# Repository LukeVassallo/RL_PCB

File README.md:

[toc]

# Project Description

RL_PCB is an end-to-end Reinforcement Learning PCB placement methodology. The solution is inspired from cellular automata. The state of the circuit placement problem is distributed across all the components on the layout region. Every component can update it's positioning independently based on local and global information. The question of how to update the state, factoring in experience (i.e. past knowledge) is a particularly difficult one. We use reinforcement learning to learn ways of updating the state. We do so in a way that localised updates are not destructive to the global solution. Consequently the solution naturally comes out as an emergent property of the system.  

You can learn more about this work by reading our [DATE 24 paper](https://ieeexplore.ieee.org/document/10546526). My [Master thesis](https://www.lukevassallo.com/wp-content/uploads/2023/09/automated_pcb_component_placement_using_rl_msc_thesis_v2_1_lv.pdf) investigated "A graph placement methodology for fast chip design" proposed by Mirhoseini et al., and based on it's shortcomings proposed this solution. 

If you find this work useful please cite us!
```bibtex
@inproceedings{Vassallo2024,
  author={Vassallo, Luke and Bajada, Josef},
  booktitle={2024 Design, Automation & Test in Europe Conference & Exhibition (DATE)}, 
  title={Learning Circuit Placement Techniques Through Reinforcement Learning with Adaptive Rewards}, 
  year={2024},
  volume={},
  number={},
  pages={1-6},
}
```

RL\_PCB is a novel learning-based method for optimising the placement of circuit components on a Printed Circuit Board (PCB). Reinforcement learning is used to learn general policies for iteratively improving a circuit placement, leading to intuitive layouts while outperforming stochastic methods in terms of post-routing wirelength.

# Key Results

The main contribution of this work is:
1. The policies learn the fundamental rules of the task and demonstrate an understanding of the problem dynamics. The agent is observed taking actions that **in the long term** minimise overlap-free wirelength. At the same time, the components naturally fall in place, resulting in a coherent layout. 
2. Since the agent represents a component, emergent behaviours are observed as a result of each component interacting with its neighbours. When we emphasise Half-Perimeter Wirelength (HPWL) in the reward function, we observe collaboration (e.g. Figure 1c, 1d); on the other hand, when we emphasise Euclidean Wirelength (EW), we observe competition (e.g. Figure 1b). 
3. The learned behaviour is robust because training data is diverse and consistent with the evaluative feedback assigned. Consistency is achieved by extensive normalisation and eliminating all potential sources introducing bias. Similarly goes for the reward. Diversity is obtained by allowing every agent to contribute to training samples with different perspectives which is further compounded by using multiple unique circuits for training - a relatively small training dataset of 6 circuits.

|     |     |     |
| --- | --- | --- |
|  <br />(a) (EW=0, HPWL=5, Overlap=5) |  <br />(b) (EW=8, HPWL=0, Overlap=2) |  <br />(c) (EW=0, HPWL=8, Overlap=2) |
|  <br />(d) (EW=0, HPWL=8, Overlap=2) |  <br />(e) (EW=8, HPWL=0, Overlap=2)|  <br />(f) (EW=8, HPWL=0, Overlap=2) |
|  <br />(g) (EW=8, HPWL=0, Overlap=2) |  <br />(h) (EW=2, HPWL=2, Overlap=6) |   <br />(i) (EW=2, HPWL=2, Overlap=6) |

**Figure 1**: Succesful policies optimising circuits not seen during training. 

# Installation Guide
**It is very important that the installation procedure is carried out while being in the root of the repository (i.e. the same location as the script install_tools_and_virtual_environment.sh)**

## Install Pre-requisites
The following packages must be installed on the system to compile libraries for parsing KiCAD PCB files (.kicad_pcb) and place-and-route tools.
```
sudo apt install python3-virtualenv build-essential libboost-dev libboost-filesystem-dev

```

To ensure consistency, Python code requires the use of version 3.8. Moreover, virtual environments for Python are necessary to install dependencies within a limited scope, preventing any modifications to the system's configuration. If Python3.8 is not available by default through the package manager of your system, you can use the following code to add an apt repository that maintains previous versions and source the required version accordingly.
```
sudo add-apt-repository ppa:deadsnakes/ppa -y
sudo apt update
sudo apt install python3.8 python3.8-venv
```

## Run automated installation script
The automated installation procedure makes the following changes to the local repository:
- Create a directory bin and installs the KiCad parsing utility, and place and route tools
- Creates an environment using python3.8, installs pytorch 1.13 with CUDA 11.7 and all necessary python packages
- Installs the wheel libraries in the lib folder

```
./install_tools_and_virtual_environment.sh --env_only
```

If you do not have CUDA 11.7 installed, you can install the CPU only. Tests an experiments will run significantly slower but works out of the box.
```
./install_tools_and_virtual_environment.sh --env_only --cpu_only
```

If you require a different version of CUDA, please make the following changes and run `install_tools_and_virtual_environment.sh` without any options:
- To `setup.sh` script, change the CUDA path to point to your installation of CUDA.
- To `install_tools_and_virtual_environment.sh` script, change the PyTorch libraries to use your CUDA version. 

Using a CPU device or alternative CUDA version will yield different results than the accompanying pdf reports for tests and experiments.

# Run tests and experiments
Always source the environment setup script before running any tests or experiments. **The script should be run from the root of the repository**
```
cd <path-to-rl_pcb>
source setup.sh 
```

Run an experiment
```
cd experiments/00_parameter_exeperiments
./run.sh    
```

Run a test - tests are used to validate the correct operation of the source code. They are periodically run in a Continuous Integration (CI) environment.
```
cd tests/01_training_td3_cpu
./run.sh
```

The script `run.sh` will perform the following: 
1. Carry out the training run(s) by following the instructions in `run_config.txt` that is located within the same directory
2. Generates an experiment report that processes the experimental data and presents the results in tables and figures. All experiment metadata is also reported, and customisation is possible through `report_config.py`, located within the same directory.
3. Evaluate all policies alongside simulated annealing baseline. All optimised placements are subsequently routed using an A\* based algorithm. 
4. Generate a report that processes all evaluation data and tabulates HPWL and routed wirelength metrics. All experiment metadata is also reported.

The generated files can be cleaned by running the following:
```
./clean.sh
```

Every test and experiment contains a directory called `expected results` that contains pre-generated reports. Should you run the experiments as provided, identical results are to be expected.

# GPU Setup (Optional)
This section provides an optional setup procedure to remove the Nvidia GPU driver and all dependent libraries and perform a fresh install. **The commands in this section make big changes to your system. Please read carefully before running commands** Some command changes will be required.

1. Remove CUDA if installed `sudo apt-get --purge remove cuda* *cublas* *cufft* *curand* *cusolver* *cusparse* *npp* *nvjpeg* *nsight*`
2. Check if the driver is installed, and if it is, remove it with `sudo apt-get --purge remove *nvidia*`
3. Remove cuddnn `sudo apt remove libcudnn* libcudnn*-dev`

### Install Nvidia GPU Driver
To install the driver, you can start by issuing the command `ubuntu-drivers devices` and identifying the latest third-party non-free version. Once you have identified the appropriate version, use `apt` to install the driver. After installing the driver, reboot your system and issue the command `nvidia-smi` to identify the full driver version. In the upcoming section, you will need this information to determine which CUDA version is supported.

### Download and install CUDA toolkit
To ensure that your device driver is compatible with CUDA, you'll need to check the compatibility using the following link: https://docs.nvidia.com/deploy/cuda-compatibility/. Once you've confirmed the compatibility, you can proceed to the CUDA Toolkit Archive at https://developer.nvidia.com/cuda-toolkit-archive. From there, select version 11.7 and choose the appropriate platform parameters from the "Select Target Platform" section. Next, download the runfile (local) and proceed with the installation process. Finally, follow the installation instructions carefully and avoid installing the driver when prompted.

```
wget https://developer.download.nvidia.com/compute/cuda/11.7.1/local_installers/cuda_11.7.1_515.65.01_linux.run
sudo sh cuda_11.7.1_515.65.01_linux.run
```

Update the setup.sh script as necessary. The default contents for `PATH` and `LD_LIBRARY_PATH` are:

```
export PATH="/usr/local/cuda-11.7/bin:$PATH"
export LD_LIBRARY_PATH="/usr/local/cuda-11.7/lib64:$LD_LIBRARY_PATH"
```

# This project is licensed under the terms of the MIT license
MIT License

Copyright (c) 2023 Luke Vassallo

Permission is hereby granted, free of charge, to any person obtaining a copy
of this software and associated documentation files (the "Software"), to deal
in the Software without restriction, including without limitation the rights
to use, copy, modify, merge, publish, distribute, sublicense, and/or sell
copies of the Software, and to permit persons to whom the Software is
furnished to do so, subject to the following conditions:

The above copyright notice and this permission notice shall be included in all
copies or substantial portions of the Software.

THE SOFTWARE IS PROVIDED "AS IS", WITHOUT WARRANTY OF ANY KIND, EXPRESS OR
IMPLIED, INCLUDING BUT NOT LIMITED TO THE WARRANTIES OF MERCHANTABILITY,
FITNESS FOR A PARTICULAR PURPOSE AND NONINFRINGEMENT. IN NO EVENT SHALL THE
AUTHORS OR COPYRIGHT HOLDERS BE LIABLE FOR ANY CLAIM, DAMAGES OR OTHER
LIABILITY, WHETHER IN AN ACTION OF CONTRACT, TORT OR OTHERWISE, ARISING FROM,
OUT OF OR IN CONNECTION WITH THE SOFTWARE OR THE USE OR OTHER DEALINGS IN THE
SOFTWARE.```

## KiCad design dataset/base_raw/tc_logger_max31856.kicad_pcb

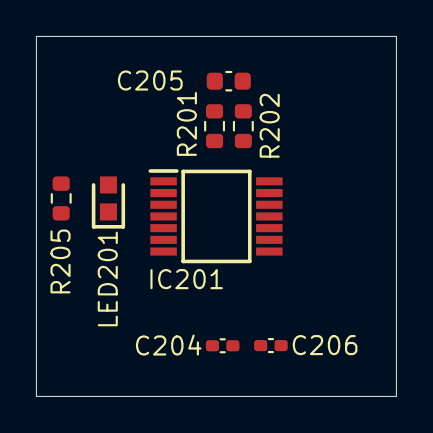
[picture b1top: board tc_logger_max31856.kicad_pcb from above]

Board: 2 copper layers, 20.0 x 20.0 mm, 8 parts (0 on the bottom side), 7 nets, no tracks yet.

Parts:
C204, C206: 0.01uF; C_0402_1005Metric_Pad0.74x0.62mm_HandSolder
C205: 0.1uF; C_0603_1608Metric
IC201: MAX31856MUD+; SOP65P640X110-14N
LED201: 150060RS75000; LEDC1608X80N
R201, R202: 100; R_0603_1608Metric
R205: 2.5k; R_0603_1608Metric

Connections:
3V3: IC201.5, IC201.8, R205.2
/thermocouple/FAULT0: IC201.13, LED201.1
/thermocouple/T0+: C205.2, C206.2, IC201.4, R202.2
/thermocouple/T0-: C204.2, C205.1, IC201.3, R201.1
GND: C204.1, C206.1, IC201.1, IC201.14
unnamed: IC201.2, R201.2
unnamed: LED201.2, R205.1

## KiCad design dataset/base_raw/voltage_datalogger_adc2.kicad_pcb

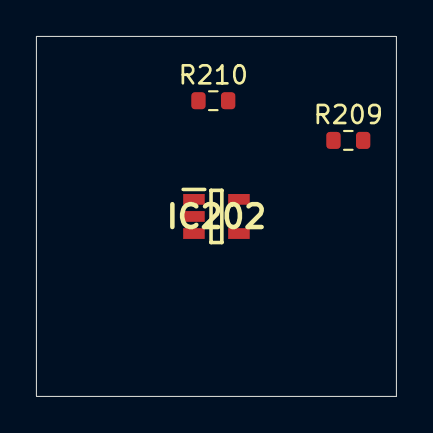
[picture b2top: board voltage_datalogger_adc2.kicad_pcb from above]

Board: 2 copper layers, 20.0 x 20.0 mm, 3 parts (0 on the bottom side), 4 nets, no tracks yet.

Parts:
IC202: TL071HIDBVR; SOT95P280X145-5N
R209, R210: 100k; R_0603_1608Metric

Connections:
/Sheet6235D886/vp: IC202.1, IC202.4
GND: IC202.2, R210.2
unnamed: IC202.3, R209.2, R210.1
VDDA: IC202.5, R209.1

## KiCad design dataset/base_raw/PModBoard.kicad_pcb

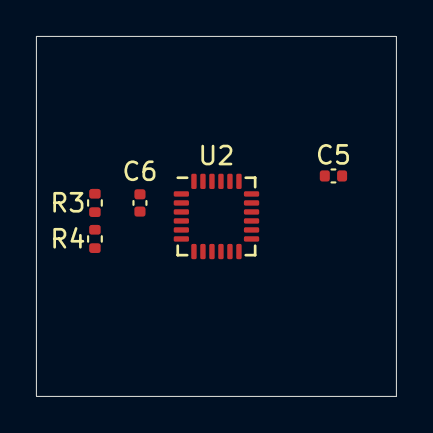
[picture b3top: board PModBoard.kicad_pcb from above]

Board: 2 copper layers, 20.0 x 20.0 mm, 5 parts (0 on the bottom side), 6 nets, no tracks yet.

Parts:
C5: 100n; C_0402_1005Metric
C6: 2n2; C_0402_1005Metric
R3, R4: 2k2; R_0402_1005Metric
U2: MPU-6050; InvenSense_QFN-24_4x4mm_P0.5mm_no_inner_grid

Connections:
+3V3: R3.1, R4.1, U2.8, U2.13
/I2C_SCL: R3.2, U2.23
/I2C_SDA: R4.2, U2.24
GND: C5.2, C6.2, U2.1, U2.9, U2.11, U2.18
unnamed: C5.1, U2.10
unnamed: C6.1, U2.20

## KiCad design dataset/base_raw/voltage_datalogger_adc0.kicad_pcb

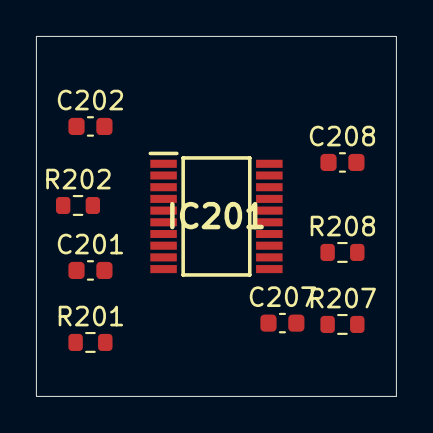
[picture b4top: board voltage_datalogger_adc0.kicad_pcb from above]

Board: 2 copper layers, 20.0 x 20.0 mm, 9 parts (0 on the bottom side), 6 nets, no tracks yet.

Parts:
C201, C202, C207, C208: 0.1uF; C_0603_1608Metric
IC201: MCP3564R-E_ST; SOP65P640X120-20N
R201, R202, R207, R208: 1k; R_0603_1608Metric

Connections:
/Sheet6235D886/ch0: C201.1, IC201.5, R201.1
/Sheet6235D886/ch1: C202.2, IC201.6, R202.1
/Sheet6235D886/ch6: C207.1, IC201.11, R207.1
/Sheet6235D886/ch7: C208.2, IC201.12, R208.1
/Sheet6235D886/vp: R201.2, R207.2
GND: C201.2, C202.1, C207.2, C208.1, IC201.2, IC201.3, IC201.19

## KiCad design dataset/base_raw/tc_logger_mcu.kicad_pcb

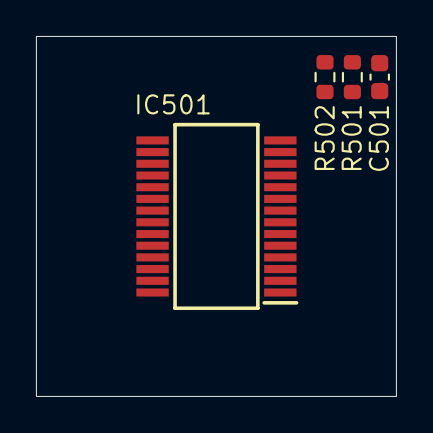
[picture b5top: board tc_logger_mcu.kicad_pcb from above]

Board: 2 copper layers, 20.0 x 20.0 mm, 4 parts (0 on the bottom side), 4 nets, no tracks yet.

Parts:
C501: 0.1uF; C_0603_1608Metric
IC501: PIC18F26Q10-I_SS; SOP65P780X200-28N
R501: 10k; R_0603_1608Metric
R502: 100; R_0603_1608Metric

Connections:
3V3: IC501.20, R501.1
/processor/ICSP_MCLR: C501.1, R501.2, R502.2
/processor/~MCLR: IC501.1, R502.1
GND: C501.2, IC501.8, IC501.19

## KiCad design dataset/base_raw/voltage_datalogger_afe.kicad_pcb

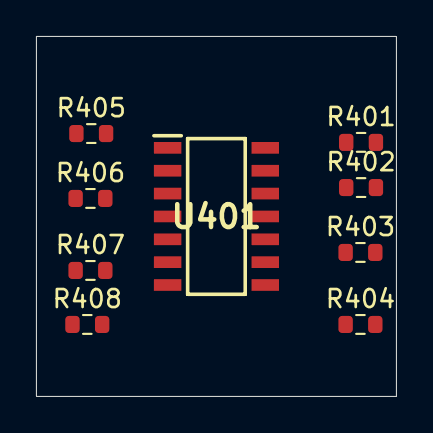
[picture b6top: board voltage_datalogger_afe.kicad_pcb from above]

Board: 2 copper layers, 20.0 x 20.0 mm, 9 parts (0 on the bottom side), 9 nets, no tracks yet.

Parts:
R401, R402, R403, R404: 10M; R_0603_1608Metric
R405, R406: 750k; R_0603_1608Metric
R407, R408: 1.5M; R_0603_1608Metric
U401: TL074; SOIC127P600X175-14N

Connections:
/Sheet6235D886/vp: R405.1, R406.1, R407.1, R408.1
/Sheet6248AD22/chn0: U401.1, U401.2
/Sheet6248AD22/chn1: U401.6, U401.7
/Sheet6248AD22/chn2: U401.8, U401.9
/Sheet6248AD22/chn3: U401.13, U401.14
unnamed: R401.2, R405.2, U401.3
unnamed: R402.2, R406.2, U401.5
unnamed: R403.2, R407.2, U401.10
unnamed: R404.2, R408.2, U401.12

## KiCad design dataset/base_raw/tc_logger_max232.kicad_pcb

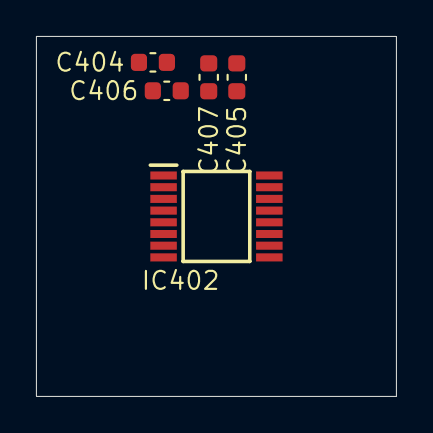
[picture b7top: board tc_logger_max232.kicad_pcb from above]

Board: 2 copper layers, 20.0 x 20.0 mm, 5 parts (0 on the bottom side), 7 nets, no tracks yet.

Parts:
C404, C405, C406, C407: 0.1uF; C_0603_1608Metric
IC402: MAX3232IPWR; SOP65P640X120-16N

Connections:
GND: C404.1, C405.1, IC402.15
unnamed: C404.2, IC402.2
unnamed: C405.2, IC402.6
unnamed: C406.1, IC402.1
unnamed: C406.2, IC402.3
unnamed: C407.1, IC402.5
unnamed: C407.2, IC402.4

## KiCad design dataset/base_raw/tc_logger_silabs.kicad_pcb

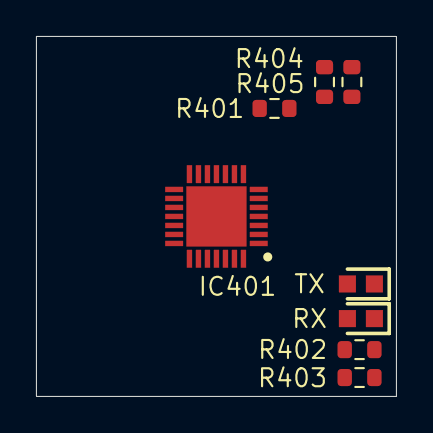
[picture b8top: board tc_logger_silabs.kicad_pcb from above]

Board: 2 copper layers, 20.0 x 20.0 mm, 8 parts (0 on the bottom side), 8 nets, no tracks yet.

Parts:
IC401: CP2102N-A02-GQFN28R; QFN50P500X500X80-29N-D
R401: 4.7k; R_0603_1608Metric
R402, R403: 750; R_0603_1608Metric
R404: 22.1k; R_0603_1608Metric
R405: 47.5k; R_0603_1608Metric
RX: 150060VS75000; LEDC1608X80N
TX: 150060VS75000; LEDC1608X80N

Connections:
3V3: IC401.6, IC401.7, R401.1, R402.2, R403.2
/serial/RXT: IC401.18, TX.1
/serial/TXT: IC401.19, RX.1
/serial/VBUS: IC401.8, R404.1, R405.2
GND: IC401.3, IC401.29, R405.1
unnamed: IC401.9, R401.2
unnamed: R402.1, RX.2
unnamed: R403.1, TX.2

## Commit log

2023-03-05 Initial commit. Most likely does not include all necessary files to perform training.
2023-03-05 Added missing files for running training
2023-03-05 Created Jenkinsfile
2023-03-05 Added python environment check script
2023-03-05 Update Jenkinsfile
2023-03-05 Updated test_setup.pu
2023-03-05 Updated scheduler.sh. Originally it was a symbolic link pointing to a file not within the repository.
2023-03-05 Added SAC.py needed by train.py
2023-03-05 Added evaluation bash scripts, and binaries for parsing, placing and routing. Updated parameter experiment too.
2023-03-07 Established baseline by configuring tests 01 and 03 for TD3/SAC training and evaluation with cpu device
2023-03-09 Update repository directory structure
2023-03-12 Updated structure and ran tests to verify correct operation. Results are not deterministic which makes it difficult to ensure the latter however good policies were learned.
2023-04-08 Updated various issues with the running of experiments. Verfied operation on ubuntu 22.04 with cuda 11.7 and pytorch 1.13.1. Updated P&R binaries after compiling on ubuntu 22.04.
2023-04-08 started tensorboard in run.sh for experiment 01
2023-04-08 Added experiments 3 (ablation w/ expert) and 4 (replay buffer sizing) albeit unverified
2023-04-13 Experiments are now deterministic.
2023-04-15 Verified that training is fully deterministic and therefore reproducable. Updated expected results of tests 02 and 04. Minor code changes to adhere to google's coding guidelines
2023-04-23 Updated expected outputs from experiments.
2023-04-23 Added updated run_config.txt for ablation experiments
2023-04-23 Added README.md with installation instructions
2023-04-26 Added fix and unit test for rare NaN occurance in direction of movement vector.
2023-04-28 Updated README.md, automatic environment generation script and setup script.
2023-04-28 Updated run.sh for test 2. Now creates work directory before starting training process
2023-04-28 Added script for building KiCAD PCB parser and PCB place and route tools.
2023-04-28 Updated script that manages utilities (e.g. kicadParser, SA_PCB and pcbRouter)
2023-04-28 Updated script last modification date.
2023-04-28 Updated test run scripts to create a work directory before launching training script. This is necessary becuase of std redirection at the beginning of the script.
2023-04-28 Added functionality to convert pcb files to png .. pending tests
2023-04-28 updated utility binary build script
2023-04-30 Updated eval_place_and_route.sh during to error in the script.
2023-04-30 Added parameter experiment using expert information
2023-04-30 Updated pcbDraw.py
2023-05-04 Updated pre-generated reports (i.e. expected results) for experiments 00 - 02
2023-05-08 Updated setup script
2023-05-10 Added new command line arguments relating to pcb_idx and redirecting stdout and stderr
2023-05-10 Updated README.md and installation script
2023-05-11 Added new test, that strictly trains on layout 4 in the dataset.
2023-05-11 Updated README.md with gifs
2023-05-11 Updated filename of gif
2023-05-11 Removed center tags around table
2023-05-11 Updated installation script and commented tensorboard video logging.
2023-05-12 Update .gitlab-ci.yml file
2023-05-12 Updated install script with absolut paths based on ${RL_PCB} environment variabled
2023-05-12 Added clean script
2023-05-12 updated clean script
2023-05-12 Updated setup and clean scripts
2023-05-12 Updated pipeline script concerning the system-test with local before_script and 12h timeout. Updated callback to use a pcb_idx of -1 for evaluation, that is to use all laayouts for evaluation, and us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
2023-05-12 updated gitlab pipeline to run two system tests, checking both cpu and gpu setups
2023-05-12 fixed error in gitlab pipeline script
2023-05-12 changed pcb_idx to idx. Changed test 6 steps from 300k to 50k
2023-05-13 Updated gitlab yaml to include artificats (experiment report + work folder)
2023-05-15 Updated artifact paths
2023-05-16 Updated report config for test 6 to point to the correct experiment. Also cleaned gitlab ci file.
2023-05-18 Cleaned train.py and TD3.py
2023-05-19 Cleaned evaluation script and updated tests 5 and 6 to run evaluation following training.
2023-05-19 updated main python scripts to return -1 when anything in the script fails. This should cause the pipeline in gitlab/jenkins to error.
2023-05-19 Updating failing script. Gitlab still does not fail the stage when python script fails ...
2023-05-19 Updated install script and gitlab pipeline script
2023-05-19 Updated gitlab ci script.
2023-05-19 More cleaning up and updated pipeline script.
2023-05-20 Linted pcb_vector_utils.py
2023-05-20 linted callbacks.py
2023-05-21 Linted several files in src/training
2023-05-21 Updated data_augmenter missing dependencies
2023-05-21 pruned pcbDraw.py
2023-05-22 linted pcbDraw.py
2023-05-22 Updated pcbDraw.py with missing dependencies and linted several files in core/agent
2023-05-23 Linted core environment and agent files. Added new fast test for SAC. Updated gitlab CI script to perform a test for SAC.
2023-05-23 Linted SAC.py. Reduced timesteps for test 06 using TD3 on CPU
2023-05-29 Linted some evaluation python scripts
2023-05-30 Linted python evaluation files. Added MIT License and subsequently updated the README.md. Added expected results for SAC test 07
2023-05-31 linted several files related to report generation
2023-06-01 Linted report generation source code
2023-06-05 Fixed error in README.md
2023-06-09 Added check for place and route binaries in all tests and experiments
2023-06-09 Updated README.md. Added python3.8 check
2023-06-10 Changed max_timesteps for test 06. It was incorrectly set to 32k.
2023-06-12 Added option to skip P&R tool installation
2023-06-12 Updated experiment 00 by removing commented code.
2023-06-12 Disabled experiment verbosity. Added a check to skip private P&R repositories during installation
2023-06-14 Updated installation with python requirements since the release 3.8.17 broke the setup.
2023-06-21 Changed greyscale videos to RGB - visually identical - due to imageio package refusing to work with a single channel images. Tensorboard now contains videos again,
2023-06-26 Updated installation script with an option to skip the repository checks
2023-08-06 Updated installation script
2023-08-07 Fixed issue causing run shceduler to terminate earlier
2023-12-31 Added ansible automatic pc setup scripts.
2024-03-16 Updated packaged that were raising security warnings
2024-03-16 removed torch packages from requirements, since these are installed manually
2024-06-16 Updated python dependencies

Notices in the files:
dataset/base_raw/tc_logger_max232.kicad_pcb:
License: Proprietry
